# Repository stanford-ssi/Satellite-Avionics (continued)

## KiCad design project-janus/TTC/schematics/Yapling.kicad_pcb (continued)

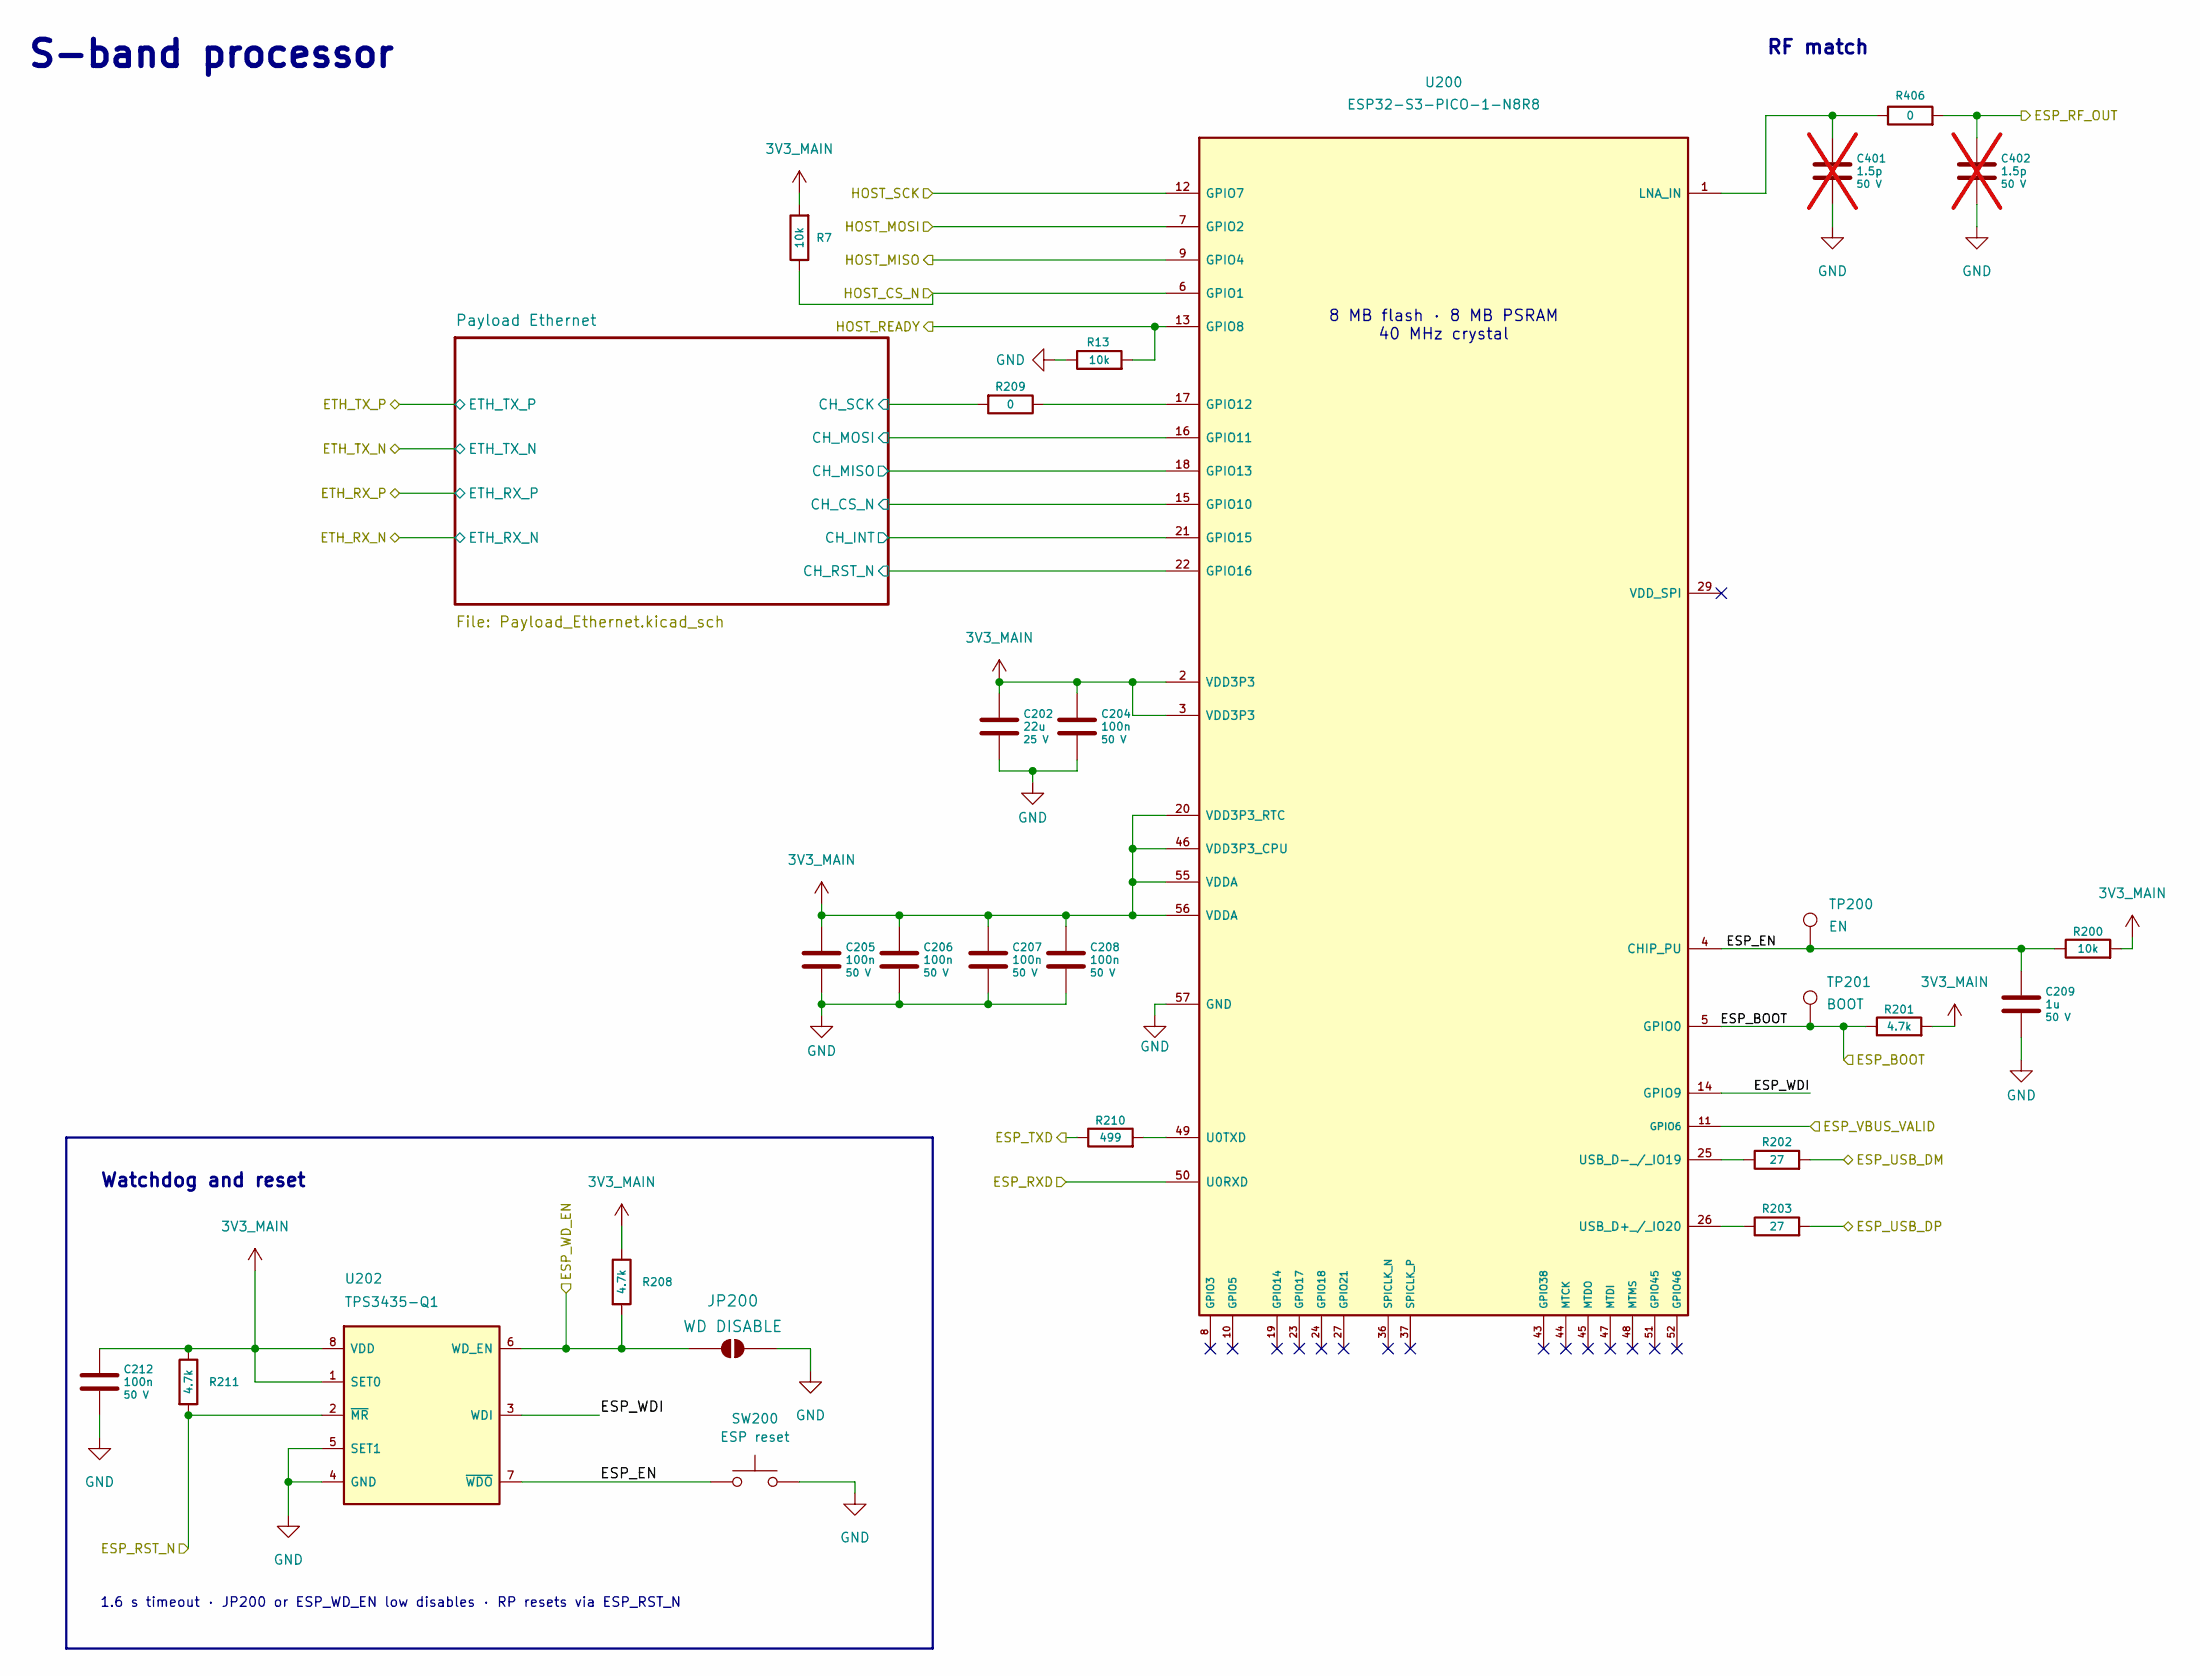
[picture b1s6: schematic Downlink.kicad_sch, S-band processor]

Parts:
C202: 22u; C_1206_3216Metric; Rating 25 V; Voltage 25 V; MPN GRM31CC71E226ME15L
C204, C205, C206, C207, C208, C212: 100n; C_0402_1005Metric; Rating 50 V; Voltage 50 V; MPN GCM155R71H104KE02D
C209: 1u; C_0603_1608Metric; Rating 50 V; Voltage 50 V; MPN CGA3E3X7R1H105K080AB
C401, C402: 1.5p; C_0201_0603Metric; Rating 50 V, C0G, ±0.1 pF; Voltage 50 V; MPN GRM0335C1H1R5BA01D; not fitted
JP200: WD DISABLE; SolderJumper-2_P1.3mm_Open_RoundedPad1.0x1.5mm
R7, R13, R200: 10k; R_0603_1608Metric; Rating 75 V; MPN TNPW060310K0BEEA
R201, R208, R211: 4.7k; R_0402_1005Metric; Rating 50 V; MPN TNPW04024K70BEED
R202, R203: 27; R_0402_1005Metric; Rating 50 V; ±1%; MPN CRCW040227R0FKED
R209: 0; R_0402_1005Metric; Rating Jumper; MPN CRCW04020000Z0ED
R210: 499; R_0402_1005Metric; Rating 50 V; MPN TNPW0402499RBEED
R406: 0; R_0201_0603Metric; Rating 1/20 W jumper; MPN CRCW02010000Z0ED
SW200: ESP reset; CK_PTS636_SK25_SMTR_LFS_GullWing_SMD; Rating 12 VDC, 50 mA; MPN PTS636 SK25 SMTR LFS; LCSC C2689642
TP200: EN; TestPoint_Pad_D1.0mm
TP201: BOOT; TestPoint_Pad_D1.0mm
U200: ESP32-S3-PICO-1-N8R8; LGA-56-1EP_7x7mm_P0.4mm_EP4x4mm; Rating 3.0–3.6 V, −40 to +65 °C (+85 °C with P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; MPN ESP32-S3-PICO-1-N8R8; LCSC C7545129
U202: TPS3435-Q1; TPS3435_DDF; Rating 1.04–6 V; open-drain watchdog; MPN TPS3435CAKAGDDFRQ1

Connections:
3V3_MAIN: C202.1, C204.1, C205.1, C206.1, C207.1, C208.1, C212.1, R7.2, R200.2, R201.2, R208.1, R211.1, U200.2 (VDD3P3), U200.3 (VDD3P3), U200.20 (VDD3P3_RTC), U200.46 (VDD3P3_CPU), U200.55 (VDDA), U200.56 (VDDA), U202.1 (SET0), U202.8 (VDD); also elsewhere on the board
/ESP32-S3 downlink/ESP_BOOT: R201.1, TP201.1 (1_1), U200.5 (GPIO0); also elsewhere on the board
/ESP32-S3 downlink/ESP_EN: C209.1, R200.1, SW200.1, TP200.1 (1_1), U200.4 (CHIP_PU), U202.7 (~WDO)
/ESP32-S3 downlink/ESP_RF_OUT: C402.1, R406.2; also elsewhere on the board
/ESP32-S3 downlink/ESP_RST_N: R211.2, U202.2 (~MR); also elsewhere on the board
/ESP32-S3 downlink/ESP_RXD: U200.50 (U0RXD); also elsewhere on the board
/ESP32-S3 downlink/ESP_TXD: R210.1; also elsewhere on the board
/ESP32-S3 downlink/ESP_USB_DM: R202.2; also elsewhere on the board
/ESP32-S3 downlink/ESP_USB_DP: R203.2; also elsewhere on the board
/ESP32-S3 downlink/ESP_VBUS_VALID: U200.11 (GPIO6); also elsewhere on the board
/ESP32-S3 downlink/ESP_WDI: U200.14 (GPIO9), U202.3 (WDI)
/ESP32-S3 downlink/ESP_WD_EN: JP200.1 (A), R208.2, U202.6 (WD_EN); also elsewhere on the board
/ESP32-S3 downlink/HOST_CS_N: R7.1, U200.6 (GPIO1); also elsewhere on the board
/ESP32-S3 downlink/HOST_MISO: U200.9 (GPIO4); also elsewhere on the board
/ESP32-S3 downlink/HOST_MOSI: U200.7 (GPIO2); also elsewhere on the board
/ESP32-S3 downlink/HOST_READY: R13.2, U200.13 (GPIO8); also elsewhere on the board
/ESP32-S3 downlink/HOST_SCK: U200.12 (GPIO7); also elsewhere on the board
/ESP32-S3 downlink/Payload Ethernet/CH_CS_N: U200.15 (GPIO10); also elsewhere on the board
/ESP32-S3 downlink/Payload Ethernet/CH_INT: U200.21 (GPIO15); also elsewhere on the board
/ESP32-S3 downlink/Payload Ethernet/CH_MISO: U200.18 (GPIO13); also elsewhere on the board
/ESP32-S3 downlink/Payload Ethernet/CH_MOSI: U200.16 (GPIO11); also elsewhere on the board
/ESP32-S3 downlink/Payload Ethernet/CH_RST_N: U200.22 (GPIO16); also elsewhere on the board
/ESP32-S3 downlink/Payload Ethernet/CH_SCK: R209.2; also elsewhere on the board
GND: C202.2, C204.2, C205.2, C206.2, C207.2, C208.2, C209.2, C212.2, C401.2, C402.2, JP200.2 (B), R13.1, SW200.2, U200.57 (GND), U202.4 (GND), U202.5 (SET1); also elsewhere on the board
unnamed: R209.1, U200.17 (GPIO12)
unnamed: C401.1, R406.1, U200.1 (LNA_IN)
unnamed: R210.2, U200.49 (U0TXD)
unnamed: R203.1, U200.26 (USB_D+_/_IO20)
unnamed: R202.1, U200.25 (USB_D−_/_IO19)

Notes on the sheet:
S-band processor
Watchdog and reset
1.6 s timeout · JP200 or ESP_WD_EN low disables · RP resets via ESP_RST_N
RF match
8 MB flash · 8 MB PSRAM 40 MHz crystal

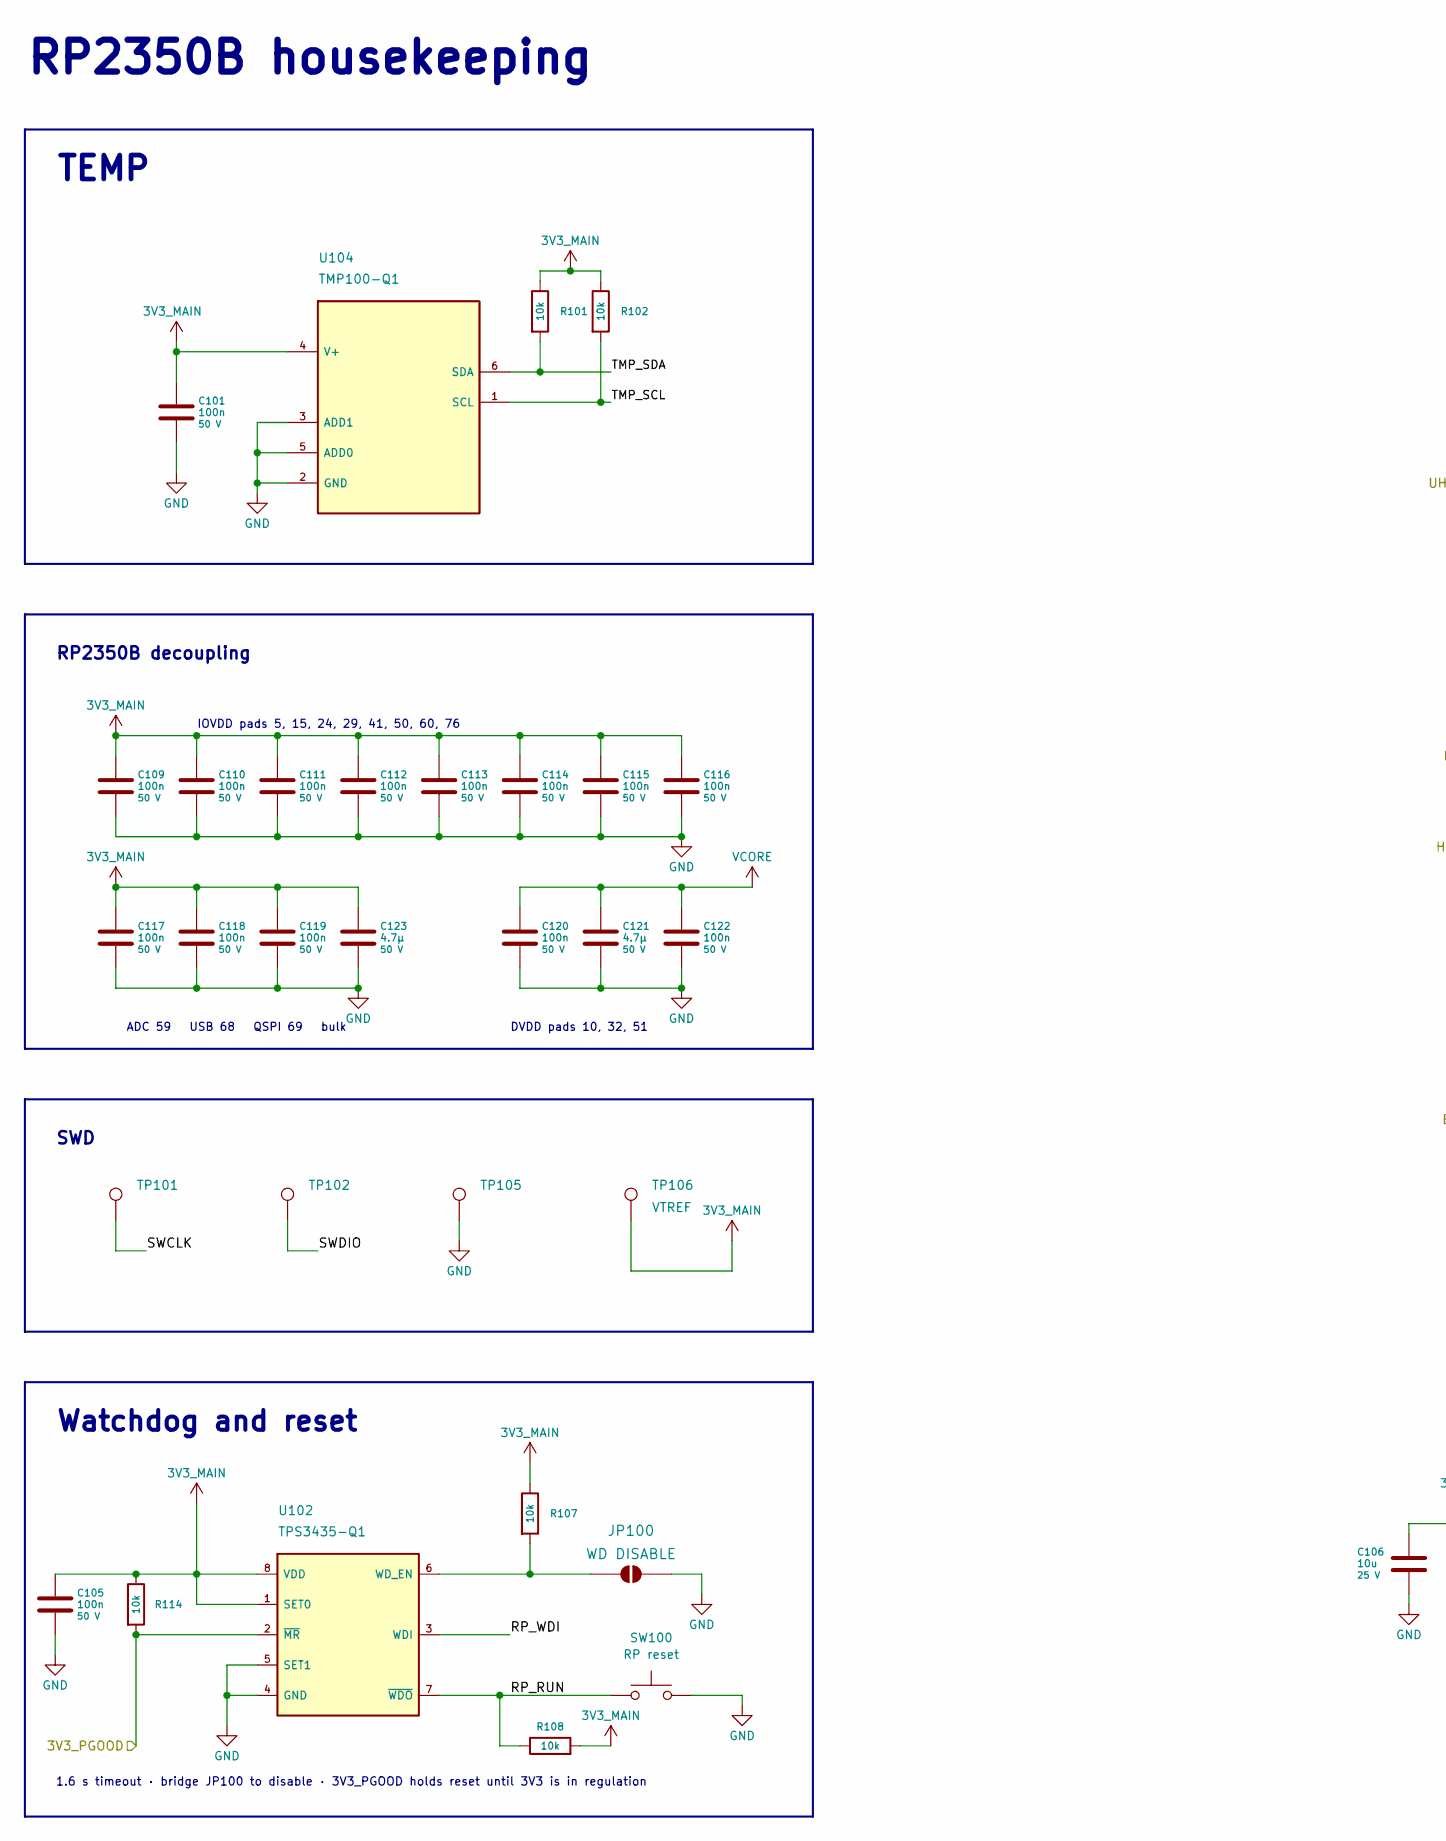
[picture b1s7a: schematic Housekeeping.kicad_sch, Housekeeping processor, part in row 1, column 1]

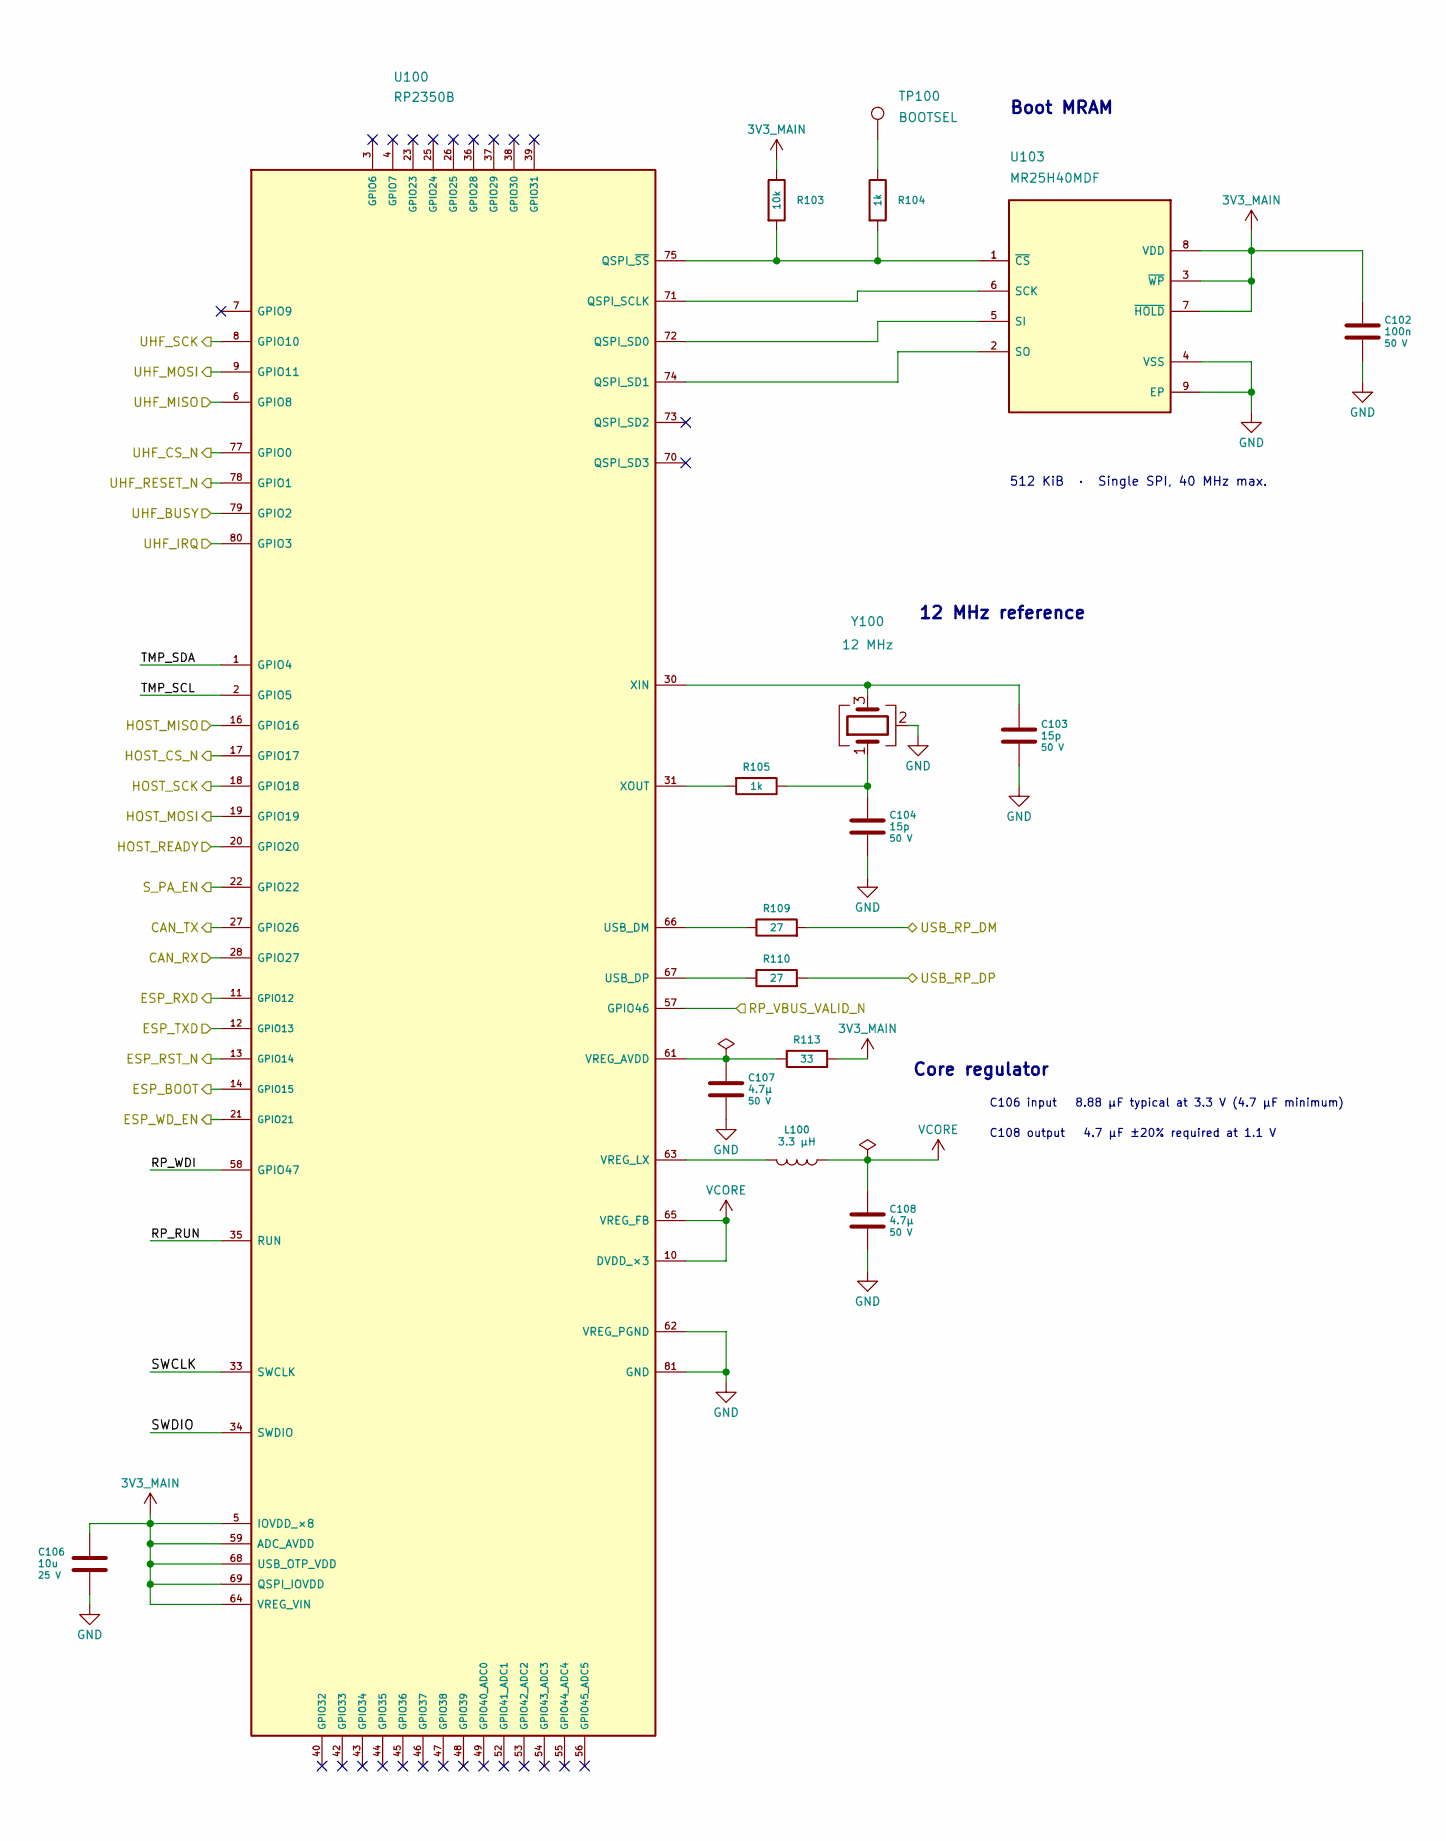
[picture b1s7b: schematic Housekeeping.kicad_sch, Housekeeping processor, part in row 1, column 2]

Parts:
C101, C102, C105, C109, C110, C111, C112, C113, C114, C115, C116, C117, C118, C119, C120, C122: 100n; C_0402_1005Metric; Rating 50 V; Voltage 50 V; MPN GCM155R71H104KE02D
C103, C104: 15p; C_0402_1005Metric; Rating 50 V C0G, ±1%; Voltage 50 V; MPN GCM1555C1H150FA16D
C106: 10u; C_0805_2012Metric; Rating 25 V; Voltage 25 V; MPN C2012X7S1E106K125AE
C107, C108, C121, C123: 4.7µ; C_0805_2012Metric; Rating 50 V; Voltage 50 V; MPN C2012X7R1H475K125AC
JP100: WD DISABLE; SolderJumper-2_P1.3mm_Open_RoundedPad1.0x1.5mm
L100: 3.3 µH; Abracon_AOTA_B201610S3R3_101_T; Rating 3.3 µH; 2.1 A; 2.4 A saturation; MPN AOTA-B201610S3R3-101-T
R101, R102, R103, R107, R108: 10k; R_0603_1608Metric; Rating 75 V; MPN TNPW060310K0BEEA
R104, R105: 1k; R_0402_1005Metric; Rating 50 V, ±0.1%; MPN TNPW04021K00BEED
R109, R110: 27; R_0402_1005Metric; Rating 50 V, ±1%; MPN CRCW040227R0FKED
R113: 33; R_0402_1005Metric; Rating 50 V, ±0.5%; MPN TNPW040233R0DEED
R114: 10k; R_0402_1005Metric; Rating 50 V; MPN TNPW040210K0BEED
SW100: RP reset; CK_PTS636_SK25_SMTR_LFS_GullWing_SMD; Rating 12 VDC, 50 mA; MPN PTS636 SK25 SMTR LFS; LCSC C2689642
TP100: BOOTSEL; TestPoint_Pad_D1.0mm
TP101: SWCLK; TestPoint_Pad_D1.0mm
TP102: SWDIO; TestPoint_Pad_D1.0mm
TP105: GND; TestPoint_Pad_D1.0mm
TP106: VTREF; TestPoint_Pad_D1.0mm
U100: RP2350B; RP2350B_R4S1; Rating 3.3 V I/O; internal core regulator; MPN SC1510-A4
U102: TPS3435-Q1; TPS3435_DDF; Rating 1.04–6 V; open-drain watchdog; MPN TPS3435CAKAGDDFRQ1
U103: MR25H40MDF; Rating 3.0–3.6 V; 4 Mbit; 40 MHz; MPN MR25H40MDF
U104: TMP100-Q1; SOT-23-6; Rating 2.7–5.5 V; −55 to +125 °C; MPN TMP100AQDBVRQ1
Y100: 12 MHz; Abracon_ABM8_3225_4Pad; Rating 12 MHz, 10 pF load, ±30 ppm; MPN ABM8-272-T3

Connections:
3V3_MAIN: C101.1, C102.1, C105.1, C106.1, C109.1, C110.1, C111.1, C112.1, C113.1, C114.1, C115.1, C116.1, C117.1, C118.1, C119.1, C123.1, R101.1, R102.1, R103.1, R107.1, R108.2, R113.2, R114.1, TP106.1 (1_1), U100.5 (IOVDD_×8), U100.15 (IOVDD), U100.24 (IOVDD), U100.29 (IOVDD), U100.41 (IOVDD), U100.50 (IOVDD), U100.59 (ADC_AVDD), U100.60 (IOVDD), U100.64 (VREG_VIN), U100.68 (USB_OTP_VDD), U100.69 (QSPI_IOVDD), U100.76 (IOVDD), U102.1 (SET0), U102.8 (VDD), U103.3 (~WP), U103.7 (~HOLD), U103.8 (VDD), U104.4 (V+); also elsewhere on the board
/Backplane connector/CAN_RX: U100.28 (GPIO27); also elsewhere on the board
/Backplane connector/CAN_TX: U100.27 (GPIO26); also elsewhere on the board
/ESP32-S3 downlink/ESP_BOOT: U100.14 (GPIO15); also elsewhere on the board
/ESP32-S3 downlink/ESP_RST_N: U100.13 (GPIO14); also elsewhere on the board
/ESP32-S3 downlink/ESP_RXD: U100.11 (GPIO12); also elsewhere on the board
/ESP32-S3 downlink/ESP_TXD: U100.12 (GPIO13); also elsewhere on the board
/ESP32-S3 downlink/ESP_WD_EN: U100.21 (GPIO21); also elsewhere on the board
/ESP32-S3 downlink/HOST_CS_N: U100.17 (GPIO17); also elsewhere on the board
/ESP32-S3 downlink/HOST_MISO: U100.16 (GPIO16); also elsewhere on the board
/ESP32-S3 downlink/HOST_MOSI: U100.19 (GPIO19); also elsewhere on the board
/ESP32-S3 downlink/HOST_READY: U100.20 (GPIO20); also elsewhere on the board
/ESP32-S3 downlink/HOST_SCK: U100.18 (GPIO18); also elsewhere on the board
/Power/3V3_PGOOD: R114.2, U102.2 (~MR); also elsewhere on the board
/Power/S_PA_EN: U100.22 (GPIO22); also elsewhere on the board
/RP2350B housekeeping/RP_RUN: R108.1, SW100.1, U100.35 (RUN), U102.7 (~WDO)
/RP2350B housekeeping/RP_VBUS_VALID_N: U100.57 (GPIO46); also elsewhere on the board
/RP2350B housekeeping/RP_WDI: U100.58 (GPIO47), U102.3 (WDI)
/RP2350B housekeeping/SWCLK: TP101.1 (1_1), U100.33 (SWCLK)
/RP2350B housekeeping/SWDIO: TP102.1 (1_1), U100.34 (SWDIO)
/RP2350B housekeeping/TMP_SCL: R102.2, U100.2 (GPIO5), U104.1 (SCL)
/RP2350B housekeeping/TMP_SDA: R101.2, U100.1 (GPIO4), U104.6 (SDA)
/RP2350B housekeeping/UHF_BUSY: U100.79 (GPIO2); also elsewhere on the board
/RP2350B housekeeping/UHF_CS_N: U100.77 (GPIO0); also elsewhere on the board
/RP2350B housekeeping/UHF_IRQ: U100.80 (GPIO3); also elsewhere on the board
/RP2350B housekeeping/UHF_MISO: U100.6 (GPIO8); also elsewhere on the board
/RP2350B housekeeping/UHF_MOSI: U100.9 (GPIO11); also elsewhere on the board
/RP2350B housekeeping/UHF_RESET_N: U100.78 (GPIO1); also elsewhere on the board
/RP2350B housekeeping/UHF_SCK: U100.8 (GPIO10); also elsewhere on the board
/RP2350B housekeeping/USB_RP_DM: R109.2; also elsewhere on the board
/RP2350B housekeeping/USB_RP_DP: R110.2; also elsewhere on the board
/RP2350B housekeeping/VCORE: C108.1, C120.1, C121.1, C122.1, L100.1, U100.10 (DVDD_×3), U100.32 (DVDD), U100.51 (DVDD), U100.65 (VREG_FB)
GND: C101.2, C102.2, C103.2, C104.2, C105.2, C106.2, C107.2, C108.2, C109.2, C110.2, C111.2, C112.2, C113.2, C114.2, C115.2, C116.2, C117.2, C118.2, C119.2, C120.2, C121.2, C122.2, C123.2, JP100.2 (B), SW100.2, TP105.1 (1_1), U100.62 (VREG_PGND), U100.81 (GND), U102.4 (GND), U102.5 (SET1), U103.4 (VSS), U103.9 (EP), U104.2 (GND), U104.3 (ADD1), U104.5 (ADD0), Y100.2 (G), Y100.4 (G); also elsewhere on the board
unnamed: C104.1, R105.1, Y100.1
unnamed: JP100.1 (A), R107.2, U102.6 (WD_EN)
unnamed: R104.1, TP100.1 (1_1)
unnamed: U100.71 (QSPI_SCLK), U103.6 (SCK)
unnamed: U100.72 (QSPI_SD0), U103.5 (SI)
unnamed: U100.74 (QSPI_SD1), U103.2 (SO)
unnamed: R103.2, R104.2, U100.75 (QSPI_~SS), U103.1 (~CS)
unnamed: R109.1, U100.66 (USB_DM)
unnamed: R110.1, U100.67 (USB_DP)
unnamed: C107.1, R113.1, U100.61 (VREG_AVDD)
unnamed: L100.2, U100.63 (VREG_LX)
unnamed: C103.1, U100.30 (XIN), Y100.3
unnamed: R105.2, U100.31 (XOUT)

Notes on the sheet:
RP2350B housekeeping
1.6 s timeout · bridge JP100 to disable · 3V3_PGOOD holds reset until 3V3 is in regulation
512 KiB · Single SPI, 40 MHz max.
Core regulator
DVDD pads 10, 32, 51
C106 input 8.88 µF typical at 3.3 V (4.7 µF minimum)
C108 output 4.7 µF ±20% required at 1.1 V
TEMP
Boot MRAM
ADC 59 USB 68 QSPI 69 bulk
SWD
RP2350B decoupling
Watchdog and reset
IOVDD pads 5, 15, 24, 29, 41, 50, 60, 76
12 MHz reference

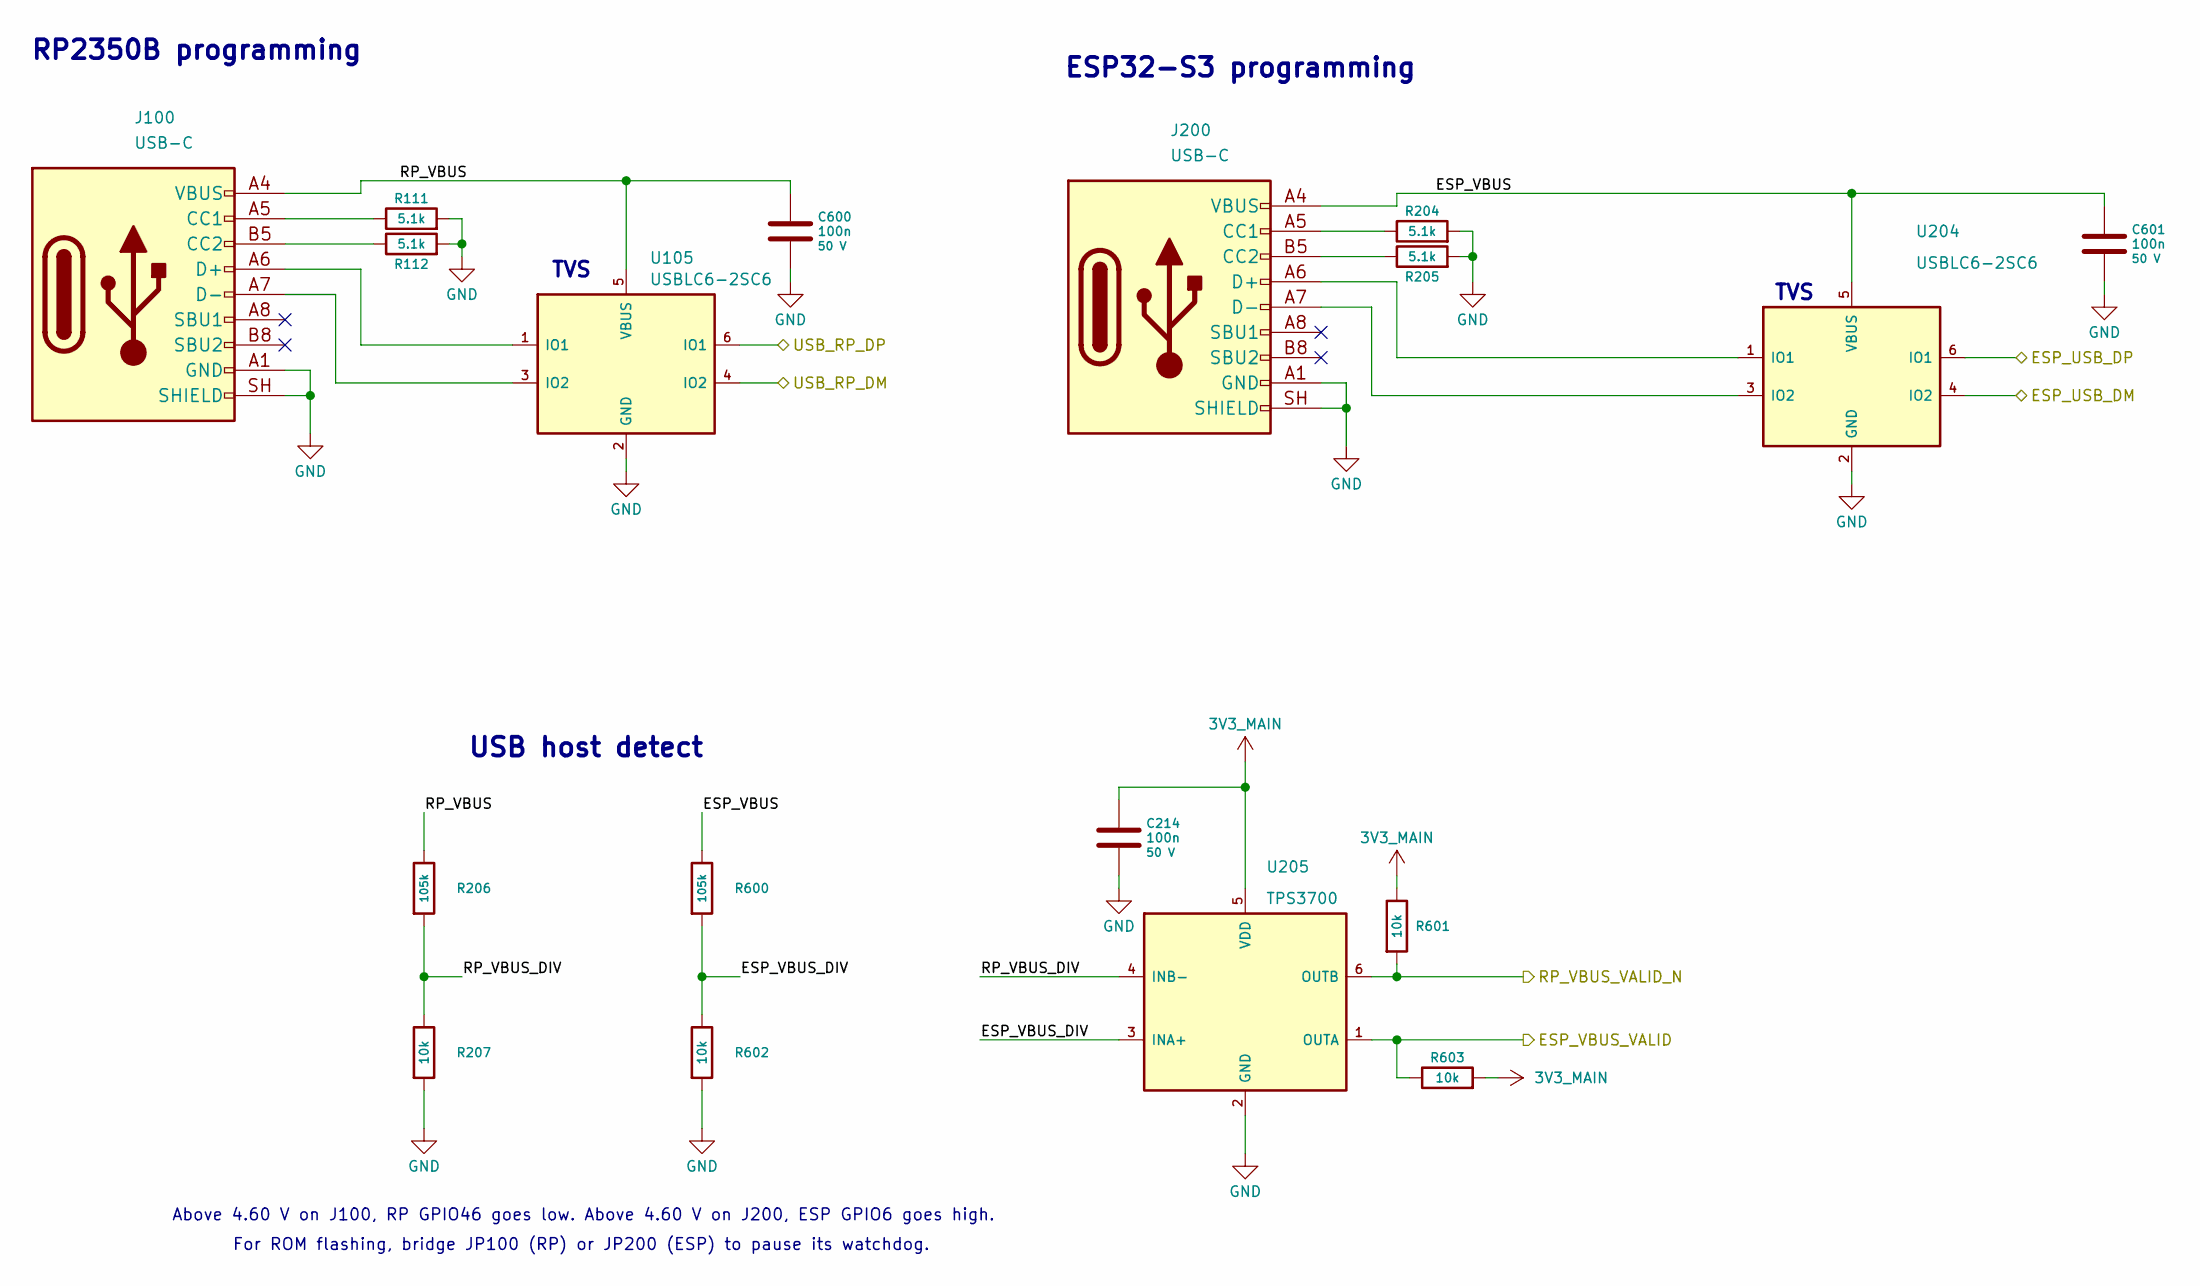
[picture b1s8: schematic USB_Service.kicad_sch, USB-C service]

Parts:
C214, C600, C601: 100n; C_0402_1005Metric; Rating 50 V; Voltage 50 V; MPN GCM155R71H104KE02D
J100, J200: USB-C; USB_C_Receptacle_GCT_USB4105-xx-A_16P_TopMnt_Horizontal; Rating USB 2.0 Type-C receptacle; 5 V nominal; MPN USB4105-GF-A
R111, R112, R204, R205: 5.1k; R_0402_1005Metric; Rating 50 V, ±0.1%; MPN TNPW04025K10BEED
R206, R600: 105k; R_0603_1608Metric; Rating 75 V; ±0.1%; MPN TNPW0603105KBEEA
R207, R601, R602, R603: 10k; R_0603_1608Metric; Rating 75 V; MPN TNPW060310K0BEEA
U105, U204: USBLC6-2SC6; Rating 5.25 V standoff; 3.5 pF max per line; MPN USBLC6-2SC6
U205: TPS3700; TI_DDC0006A; Rating 1.8–18 V; 400 mV threshold; MPN TPS3700DDCR

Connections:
3V3_MAIN: C214.1, R601.1, R603.2, U205.5 (VDD); also elsewhere on the board
/ESP32-S3 downlink/ESP_USB_DM: U204.4 (IO2); also elsewhere on the board
/ESP32-S3 downlink/ESP_USB_DP: U204.6 (IO1); also elsewhere on the board
/ESP32-S3 downlink/ESP_VBUS_VALID: R603.1, U205.1 (OUTA); also elsewhere on the board
/RP2350B housekeeping/RP_VBUS_VALID_N: R601.2, U205.6 (OUTB); also elsewhere on the board
/RP2350B housekeeping/USB_RP_DM: U105.4 (IO2); also elsewhere on the board
/RP2350B housekeeping/USB_RP_DP: U105.6 (IO1); also elsewhere on the board
/USB-C service ports/ESP_VBUS: C601.1, J200.A4 (VBUS), J200.A9 (VBUS), J200.B4 (VBUS), J200.B9 (VBUS), R600.1, U204.5 (VBUS)
/USB-C service ports/ESP_VBUS_DIV: R600.2, R602.1, U205.3 (INA+)
/USB-C service ports/RP_VBUS: C600.1, J100.A4 (VBUS), J100.A9 (VBUS), J100.B4 (VBUS), J100.B9 (VBUS), R206.1, U105.5 (VBUS)
/USB-C service ports/RP_VBUS_DIV: R206.2, R207.1, U205.4 (INB−)
GND: C214.2, C600.2, C601.2, J100.A1 (GND), J100.A12 (GND), J100.B1 (GND), J100.B12 (GND), J100.SH (SHIELD), J200.A1 (GND), J200.A12 (GND), J200.B1 (GND), J200.B12 (GND), J200.SH (SHIELD), R111.2, R112.2, R204.2, R205.2, R207.2, R602.2, U105.2 (GND), U204.2 (GND), U205.2 (GND); also elsewhere on the board
unnamed: J100.A5 (CC1), R111.1
unnamed: J100.B5 (CC2), R112.1
unnamed: J100.A6 (D+), J100.B6 (D+), U105.1 (IO1)
unnamed: J100.A7 (D-), J100.B7 (D-), U105.3 (IO2)
unnamed: J200.A5 (CC1), R204.1
unnamed: J200.B5 (CC2), R205.1
unnamed: J200.A6 (D+), J200.B6 (D+), U204.1 (IO1)
unnamed: J200.A7 (D-), J200.B7 (D-), U204.3 (IO2)

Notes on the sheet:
USB host detect
For ROM flashing, bridge JP100 (RP) or JP200 (ESP) to pause its watchdog.
TVS
Above 4.60 V on J100, RP GPIO46 goes low. Above 4.60 V on J200, ESP GPIO6 goes high.
RP2350B programming
ESP32-S3 programming

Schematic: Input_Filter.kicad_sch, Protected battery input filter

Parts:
C21: 1u; C_0603_1608Metric; Rating 50 V; Voltage 50 V; MPN CGA3E3X7R1H105K080AB
C22, C23: 22u; C_1206_3216Metric; Rating 25 V; Voltage 25 V; MPN GRM31CC71E226ME15L
D1: SMBJ9.0A; D_SMB; Rating 9 V standoff; 15.4 V max at 39 A; MPN SMBJ9.0A
L3: 2.2uH; L_Coilcraft_XAL5030-XXX; Rating 2.2 µH, 20%; MPN XAL5030-222MEC
R8: 680m; R_1206_3216Metric; Rating 0.68 Ω, 1%, 0.25 W; MPN ERJ-8RQFR68V

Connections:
GND: C21.2, C22.2, C23.2, D1.2 (A); also elsewhere on the board
unnamed: C22.1, C23.1, R8.2
VBAT_FILTERED: L3.2, R8.1; also elsewhere on the board
VBAT_PROT: C21.1, D1.1 (K), L3.1; also elsewhere on the board

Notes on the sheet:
Ripple current reaching the PDU
PDU current / injected VIN current · 2 MHz nominal: −118 dB
Solid: nominal model Shaded: component and harness corners
Filter output impedance at buck VIN
Filter peak 0.94 Ω · converter input estimate 2.34 Ω
Model includes C2 and C3 at buck VIN.
Protected battery input

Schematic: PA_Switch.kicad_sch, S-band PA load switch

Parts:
C15: 1u; C_0603_1608Metric; Rating 50 V; Voltage 50 V; MPN CGA3E3X7R1H105K080AB
C18: 1n; C_0402_1005Metric; Rating 50 V C0G; Voltage 50 V; MPN GRM1555C1H102JA01D
C20: 4.7u; C_0805_2012Metric; Rating 50 V; Voltage 50 V; MPN C2012X7R1H475K125AC
R6: 10k; R_0603_1608Metric; Rating 75 V; MPN TNPW060310K0BEEA
U3: TPS22965-Q1; Texas_DSG0008A_WSON-8-1EP_2x2mm_P0.5mm_EP0.9x1.6mm; Rating 0.8–5.5 V VIN, 4 A; MPN TPS22965TDSGRQ1

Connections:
5V_PA_SW: C15.1, U3.7 (VOUT), U3.8 (VOUT); also elsewhere on the board
5V_RF: C20.1, U3.1 (VIN), U3.2 (VIN), U3.4 (VBIAS); also elsewhere on the board
/Power/S_PA_EN: R6.1, U3.3 (ON); also elsewhere on the board
GND: C15.2, C18.2, C20.2, R6.2, U3.5 (GND), U3.9 (EP); also elsewhere on the board
unnamed: C18.1, U3.6 (CT)

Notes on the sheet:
S-band PA load switch

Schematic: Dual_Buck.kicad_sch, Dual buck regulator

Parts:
C1: 4.7u; C_0805_2012Metric; Rating 50 V; Voltage 50 V; MPN C2012X7R1H475K125AC
C2, C3, C8, C9, C12, C13: 22u; C_1206_3216Metric; Rating 25 V; Voltage 25 V; MPN GRM31CC71E226ME15L
C6, C7, C10, C11: 100n; C_0402_1005Metric; Rating 50 V; Voltage 50 V; MPN GCM155R71H104KE02D
L1, L2: 2.2uH; L_Coilcraft_XAL5030-XXX; Rating 2.2 µH, 20%; MPN XAL5030-222MEC
R1: 45.3k; R_0603_1608Metric; Rating 75 V; MPN TNPW060345K3BEEA
R2, R4: 10k; R_0603_1608Metric; Rating 75 V; MPN TNPW060310K0BEEA
R3: 71.5k; R_0603_1608Metric; Rating 75 V; MPN TNPW060371K5BEEA
U1: LTC3633A; QFN-28-1EP_4x5mm_P0.5mm_EP2.65x3.65mm; Rating 3.6–20 V input; MPN LTC3633AIUFD#PBF

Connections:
3V3_MAIN: C8.1, C9.1, L1.2, R1.1, U1.25 (VON1); also elsewhere on the board
5V_RF: C12.1, C13.1, L2.2, R3.1, U1.12 (VON2); also elsewhere on the board
/Power/3V3_PGOOD: U1.1 (PGOOD1); also elsewhere on the board
GND: C1.2, C2.2, C3.2, C6.2, C8.2, C9.2, C10.2, C12.2, C13.2, R2.2, R4.2, U1.7 (SGND), U1.29 (PGND); also elsewhere on the board
unnamed: C7.2, L1.1, U1.23 (SW1), U1.24 (SW1)
unnamed: C11.2, L2.1, U1.13 (SW2), U1.14 (SW2)
unnamed: C7.1, U1.20 (BOOST1)
unnamed: C11.1, U1.17 (BOOST2)
unnamed: C1.1, U1.2 (PHMODE), U1.4 (MODE/SYNC), U1.5 (RT), U1.11 (ITH2), U1.18 (V2P5), U1.19 (INTVCC), U1.26 (ITH1)
unnamed: C6.1, U1.27 (TRACKSS1)
unnamed: C10.1, U1.10 (TRACKSS2)
unnamed: R1.2, R2.1, U1.28 (VFB1)
unnamed: R3.2, R4.1, U1.9 (VFB2)
VBAT_FILTERED: C2.1, C3.1, U1.3 (RUN1), U1.6 (RUN2), U1.15 (VIN2), U1.16 (VIN2), U1.21 (VIN1), U1.22 (VIN1); also elsewhere on the board

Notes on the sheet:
C2 at VIN1, C3 at VIN2 · 18.9 µF combined at 8.4 V
4.890 V · 1.87 mV p-p · 25.9 µF
Dual buck regulator
3.318 V · 1.73 mV p-p · 29.7 µF

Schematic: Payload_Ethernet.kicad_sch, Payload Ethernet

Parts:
C301: 10u; C_0805_2012Metric; Rating 25 V; Voltage 25 V; MPN C2012X7S1E106K125AE
C302, C303: 100n; C_0402_1005Metric; Rating 50 V; Voltage 50 V; MPN GCM155R71H104KE02D
C304, C305, C306: 1u; C_0603_1608Metric; Rating 50 V; Voltage 50 V; MPN CGA3E3X7R1H105K080AB
C307: 1n; C_1808_4520Metric; Rating 2 kV DC; Voltage 2 kV; MPN C4520X7R3D102K130KA
R301, R302: 75; R_0603_1608Metric; Rating 75 V; MPN TNPW060375R0BEEA
T301: HX1188NLT; Rating 1500 Vrms isolation, −40 to +85 °C; MPN HX1188NLT
U301: CH390D; Rating 3.3 V; MPN CH390D
Y301: 25 MHz; ABM8; Rating 25 MHz, 12 pF, ±10 ppm initial, ±20 ppm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; MPN ABM8-25.000MHZ-12-D1X-T

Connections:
3V3_MAIN: C301.1, C302.1, C303.1, U301.6 (AVDD33_/_VDDIO), U301.10 (AVDD33); also elsewhere on the board
/Backplane connector/ETH_RX_N: T301.9 (RX−); also elsewhere on the board
/Backplane connector/ETH_RX_P: T301.11 (RX+); also elsewhere on the board
/Backplane connector/ETH_TX_N: T301.14 (TX−); also elsewhere on the board
/Backplane connector/ETH_TX_P: T301.16 (TX+); also elsewhere on the board
/ESP32-S3 downlink/Payload Ethernet/CH_CS_N: U301.11 (~SCS); also elsewhere on the board
/ESP32-S3 downlink/Payload Ethernet/CH_INT: U301.14 (INT); also elsewhere on the board
/ESP32-S3 downlink/Payload Ethernet/CH_MISO: U301.9 (SDO); also elsewhere on the board
/ESP32-S3 downlink/Payload Ethernet/CH_MOSI: U301.13 (SDI); also elsewhere on the board
/ESP32-S3 downlink/Payload Ethernet/CH_RST_N: U301.18 (~RSTB); also elsewhere on the board
/ESP32-S3 downlink/Payload Ethernet/CH_SCK: U301.12 (SCK); also elsewhere on the board
GND: C301.2, C302.2, C303.2, C304.2, C305.2, C306.2, C307.2, U301.0 (GND_/_EP), Y301.2 (G), Y301.4 (G); also elsewhere on the board
unnamed: C307.1, R301.2, R302.2
unnamed: R302.1, T301.10 (CMR)
unnamed: R301.1, T301.15 (CMT)
unnamed: C306.1, T301.7 (RCT)
unnamed: T301.6 (RD+), U301.2 (MDIRP)
unnamed: T301.8 (RD−), U301.3 (MDIRN)
unnamed: C305.1, T301.2 (TCT)
unnamed: T301.1 (TD+), U301.4 (MDITP)
unnamed: T301.3 (TD−), U301.5 (MDITN)
unnamed: C304.1, U301.1 (VDDK), U301.8 (RSVD)
unnamed: U301.19 (XI), Y301.1
unnamed: U301.20 (XO), Y301.3

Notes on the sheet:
Payload Ethernet
100BASE-TX
